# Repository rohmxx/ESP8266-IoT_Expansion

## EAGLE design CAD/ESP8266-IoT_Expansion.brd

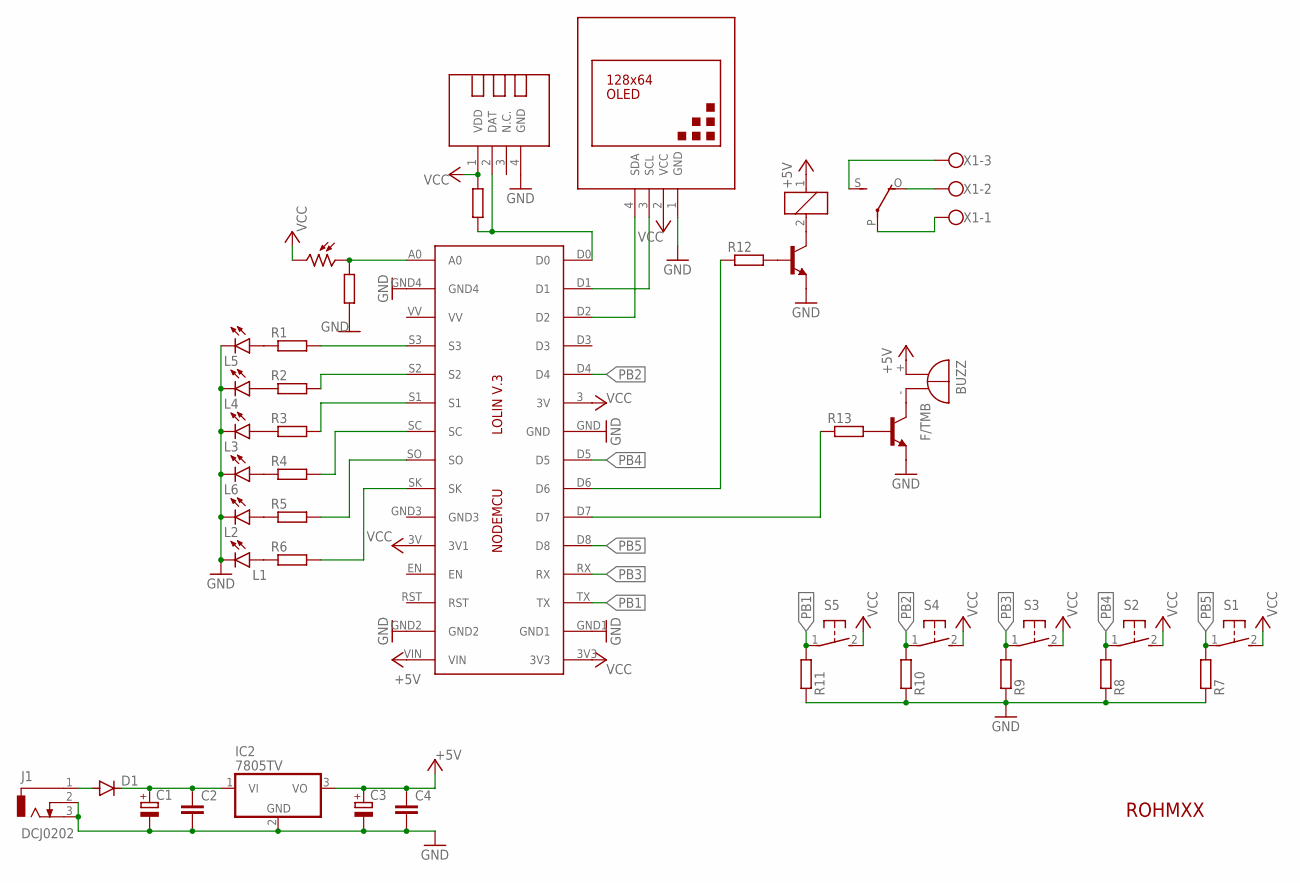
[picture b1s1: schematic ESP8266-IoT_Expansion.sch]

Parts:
BUZZ: F/TMB
C1, C3: CPOL-EUE5-10.5; E5-10,5
C2, C4: C-EU075-032X103; C075-032X103
D1: 1N4007; DO35-7
DHT-11: TEMP-HUM-SENSOR-DHT11
IC1: LOLINV3
IC2: 7805TV; TO220V
J1: DCJ0202
K1: G5LE
L1, L2, L3, L4, L5, L6: LED3MM
LDR: V1060_21; TO-5_V10
R1, R2, R3, R4, R5, R6, R7, R8, R9, R10, R11, R12, R13, R14, R15: R-EU_0207/7; 0207/7
S1, S2, S3, S4, S5: DTS-3
T1, T2: 2N3904; TO92
U$1: DISPLAY-OLED-128X64-I2C
X1: W237-103

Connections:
+5V: BUZZ.+, C3.+, C4.1, IC1.VIN, IC2.3 (VO), K1.1
GND: C1.-, C2.2, C3.-, C4.2, DHT-11.4 (GND), IC1.GND, IC1.GND1, IC1.GND2, IC1.GND4, IC2.2 (GND), J1.2, J1.3, L1.K (C), L2.K (C), L3.K (C), L4.K (C), L5.K (C), L6.K (C), R7.1, R8.1, R9.1, R10.1, R11.1, R14.1, T1.3 (E), T2.3 (E), U$1.1 (GND)
unnamed: L5.A, R1.1
unnamed: L4.A, R2.1
unnamed: L3.A, R3.1
unnamed: L6.A, R4.1
unnamed: L2.A, R5.1
unnamed: L1.A, R6.1
unnamed: R13.2, T1.2 (B)
unnamed: BUZZ.-, T1.1 (C)
unnamed: R12.2, T2.2 (B)
unnamed: K1.2, T2.1 (C)
unnamed: IC1.A0, LDR.1, R14.2
unnamed: K1.O, X1.2
unnamed: K1.S, X1.3
unnamed: DHT-11.2 (DAT), IC1.D0, R15.2
unnamed: K1.P, X1.1
unnamed: IC1.S3, R1.2
unnamed: IC1.S2, R2.2
unnamed: IC1.S1, R3.2
unnamed: IC1.SC, R4.2
unnamed: IC1.SO, R5.2
unnamed: IC1.SK, R6.2
unnamed: C1.+, C2.1, D1.C, IC2.1 (VI)
unnamed: IC1.D7, R13.1
unnamed: IC1.D6, R12.1
unnamed: D1.A, J1.1
unnamed: IC1.D2, U$1.4 (SDA)
unnamed: IC1.D1, U$1.3 (SCL)
PB1: IC1.TX, R11.2, S5.1
PB2: IC1.D4, R10.2, S4.1
PB3: IC1.RX, R9.2, S3.1
PB4: IC1.D5, R8.2, S2.1
PB5: IC1.D8, R7.2, S1.1
VCC: DHT-11.1 (VDD), IC1.3 (3V), IC1.3V (3V1), IC1.3V3, LDR.2, R15.1, S1.2, S2.2, S3.2, S4.2, S5.2, U$1.2 (VCC)

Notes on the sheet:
ROHMXX

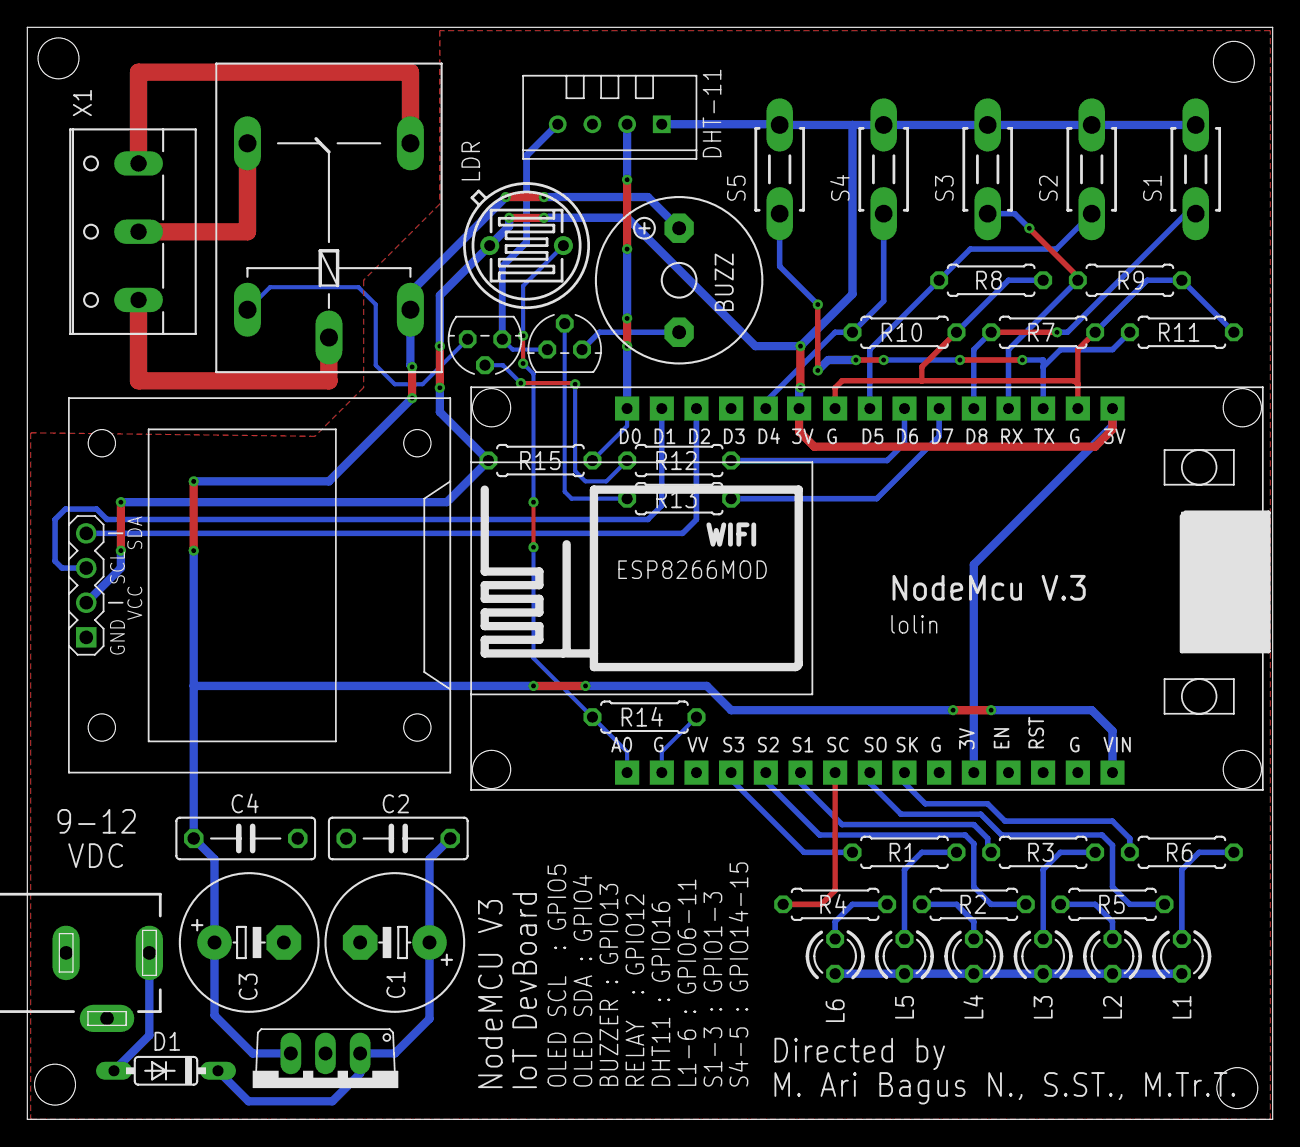
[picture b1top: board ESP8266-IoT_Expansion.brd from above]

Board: 2 copper layers, 91.2 x 80.0 mm, 42 parts (0 on the bottom side), 35 nets.

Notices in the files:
parts and their libraries:
diy-modules: Released under the Creative Commons Attribution 4.0 International License: http://creativecommons.org/licenses/by/4.0
